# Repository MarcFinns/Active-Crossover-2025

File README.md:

## Active crossover and anti-pop

Used to transform old speakers into active monitors together with a TPA3116 stereo amp board and a 24V power supply from Aliexpress

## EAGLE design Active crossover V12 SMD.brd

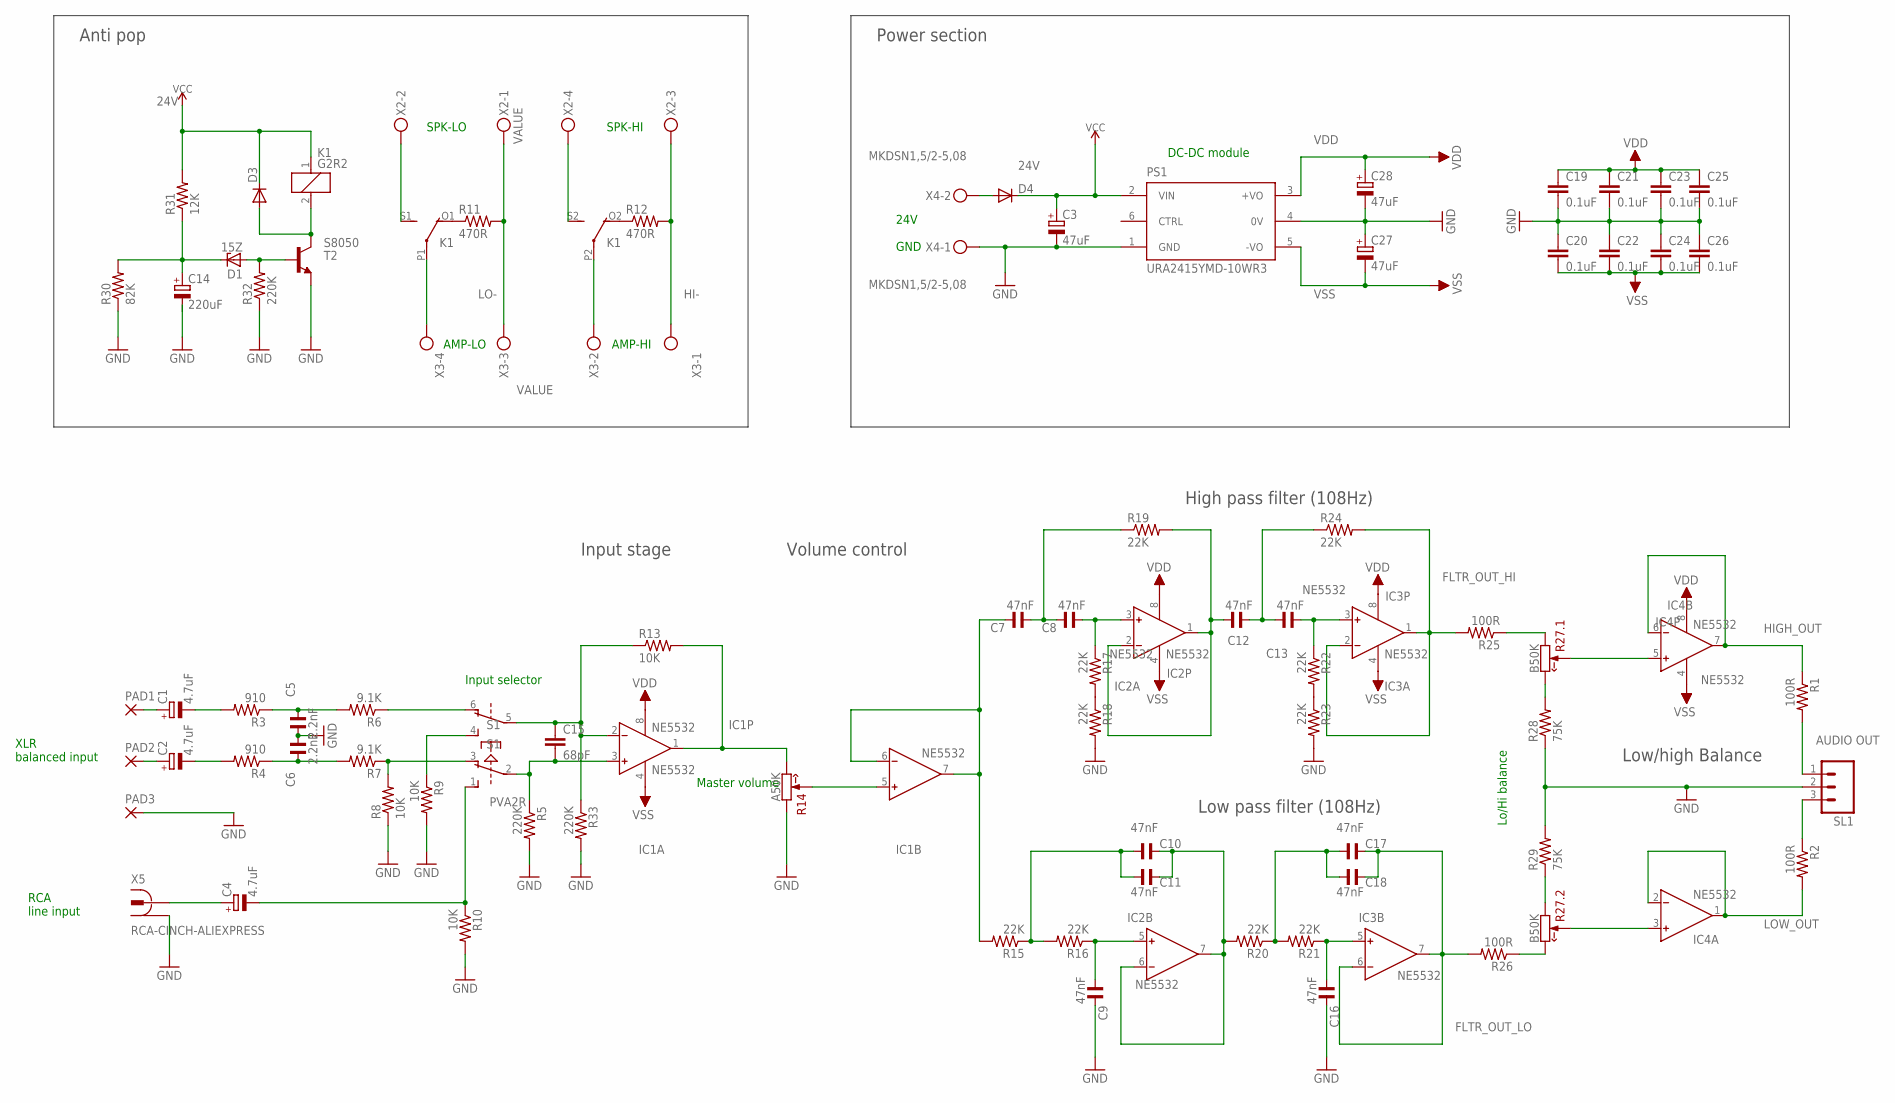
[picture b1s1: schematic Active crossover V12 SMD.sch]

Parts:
C1, C2, C4: 4.7uF; E2-5
C3, C27, C28: 47uF; E2,5-6
C5, C6: 2.2nF; C050-025X072
C7, C8, C9, C10, C11, C12, C13, C16, C17, C18: 47nF; C050-025X072
C14: 220uF; E3,5-8
C15: 68pF; 0603-CAP
C19, C20, C21, C22, C23, C24, C25, C26: 0.1uF; 0603-CAP
D1: 15Z; ZDIO-7.5
D3: DIODESMA-ALT; SMA-DIODE_ALT
D4: DIODESMB; SMB-DIODE
IC1, IC2, IC3, IC4: NE5532; DIL08
K1: G2R2
PAD1, PAD2, PAD3: 3,17/1,3
PS1: URA2415YMD-10WR3; CONV_URA2405YMD-10WR3
R1, R2, R25, R26: 100R; 0204/7
R3, R4: 910; 0204/7
R5, R33: 220K; 0204/7
R6, R7: 9.1K; 0204/7
R8, R9, R10, R13: 10K; 0204/7
R11, R12: 470R; 0204/7
R14: A50K; RV09-SINGLE
R15, R16, R17, R18, R19, R20, R21, R22, R23, R24: 22K; 0204/7
R27: B50K; RK14-DUAL
R28, R29: 75K; 0204/7
R30: 82K; M0805
R31: 12K; M0805
R32: 220K; M0805
S1: PVA2R
SL1: AUDIO OUT; 03P
T2: S8050; SOT23
X2, X3: MKDSN1,5/4-5,08
X4: MKDSN1,5/2-5,08
X5: RCA-CINCH-ALIEXPRESS

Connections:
24V: C3.+, D3.C, D4.C, K1.1, PS1.2 (VIN), R31.2
FLTR_OUT_HI: IC3.1 (OUT), IC3.2 (IN-), R24.2, R25.2
FLTR_OUT_LO: C17.2, C18.2, IC3.6 (IN-), IC3.7 (OUT), R26.2
GND: C3.-, C5.1, C6.2, C9.2, C14.-, C16.2, C19.2, C20.1, C21.2, C22.1, C23.2, C24.1, C25.2, C26.1, C27.+, C28.-, PAD3.1, PS1.1 (GND), PS1.4 (0V), R5.2, R8.1, R9.2, R10.2, R14.1 (CCW), R18.2, R23.2, R28.1, R29.2, R30.1, R32.1, R33.2, SL1.2, T2.2 (E), X4.1, X5.P$1 (1), X5.P$3 (1)
HI-: R12.2, X2.3, X3.1
HIGH_OUT: IC4.6 (IN-), IC4.7 (OUT), R1.1
LO-: R11.2, X2.1, X3.3
LOW_OUT: IC4.1 (OUT), IC4.2 (IN-), R2.2
unnamed: C1.+, PAD1.1
unnamed: C1.-, R3.2
unnamed: R7.1, R8.2, S1.3 (O)
unnamed: C15.1, IC1.2 (IN-), R13.1, R33.1, S1.5
unnamed: C15.2, IC1.3 (IN+), R5.1, S1.2
unnamed: C4.-, R10.1, S1.1 (S)
unnamed: R6.1, S1.6 (O)
unnamed: R9.1, S1.4 (S)
unnamed: IC1.1 (OUT), R13.2, R14.3 (CW)
unnamed: C14.+, D1.C, R30.2, R31.1
unnamed: K1.P1, X3.4
unnamed: D1.A, R32.2, T2.1 (B)
unnamed: D3.A, K1.2, T2.3 (C)
unnamed: IC1.5 (IN+), R14.2 (W)
unnamed: K1.S1 (S), X2.2
unnamed: C16.1, IC3.5 (IN+), R21.1
unnamed: C5.2, R3.1, R6.2
unnamed: C6.1, R4.1, R7.2
unnamed: C10.1, C11.1, R15.1, R16.2
unnamed: C17.1, C18.1, R20.1, R21.2
unnamed: C8.1, IC2.3 (IN+), R17.1
unnamed: C7.1, C8.2, R19.1
unnamed: R27.3 (CCW), R29.1
unnamed: C9.1, IC2.5 (IN+), R16.1
unnamed: R27.1' (CW), R28.2
unnamed: C12.2, IC2.1 (OUT), IC2.2 (IN-), R19.2
unnamed: C12.1, C13.2, R24.1
unnamed: C13.1, IC3.3 (IN+), R22.1
unnamed: C10.2, C11.2, IC2.6 (IN-), IC2.7 (OUT), R20.2
unnamed: K1.O1 (O), R11.1
unnamed: K1.P2, X3.2
unnamed: K1.S2 (S), X2.4
unnamed: K1.O2 (O), R12.1
unnamed: R17.2, R18.1
unnamed: C7.2, IC1.6 (IN-), IC1.7 (OUT), R15.2
unnamed: R22.2, R23.1
unnamed: R25.1, R27.3' (CCW)
unnamed: IC4.5 (IN+), R27.2' (W)
unnamed: IC4.3 (IN+), R27.2 (W)
unnamed: R26.1, R27.1 (CW)
unnamed: C2.+, PAD2.1
unnamed: C2.-, R4.2
unnamed: C4.+, X5.P$2 (2)
unnamed: D4.A, X4.2
unnamed: R1.2, SL1.1
unnamed: R2.1, SL1.3
VDD: C19.1, C21.1, C23.1, C25.1, C28.+, IC1.8 (V+), IC2.8 (V+), IC3.8 (V+), IC4.8 (V+), PS1.3 (+VO)
VSS: C20.2, C22.2, C24.2, C26.2, C27.-, IC1.4 (V-), IC2.4 (V-), IC3.4 (V-), IC4.4 (V-), PS1.5 (-VO)

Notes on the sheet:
XLR balanced input
RCA line input
Input selector
Master volume
AMP-LO
AMP-HI
SPK-LO
SPK-HI
24V GND
DC-DC module
Lo/Hi balance
Anti pop
Power section
Input stage
Volume control
High pass filter (108Hz)
Low pass filter (108Hz)
Low/high Balance

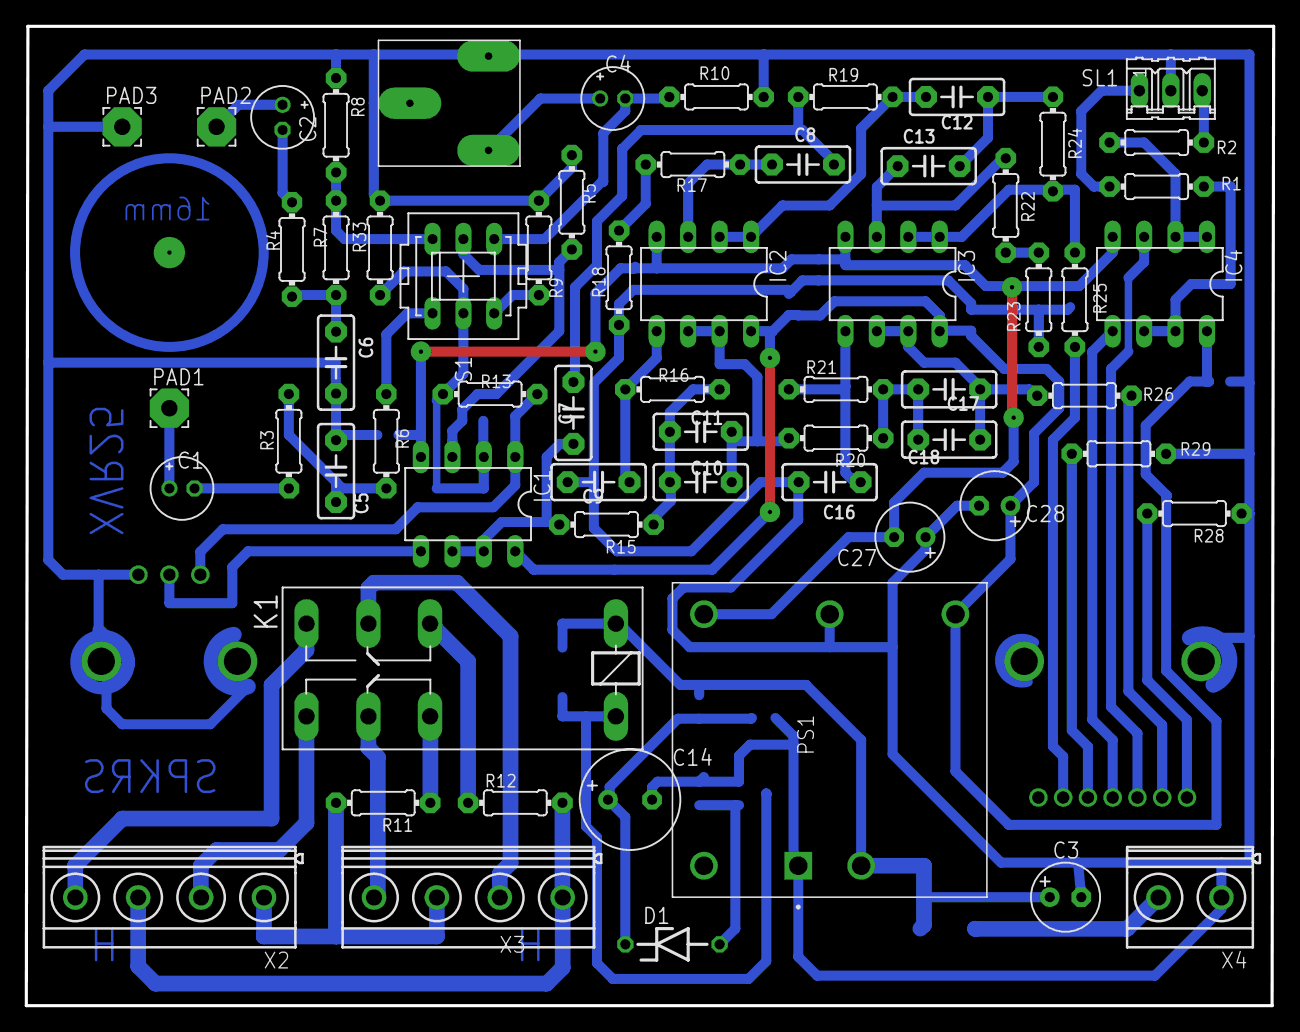
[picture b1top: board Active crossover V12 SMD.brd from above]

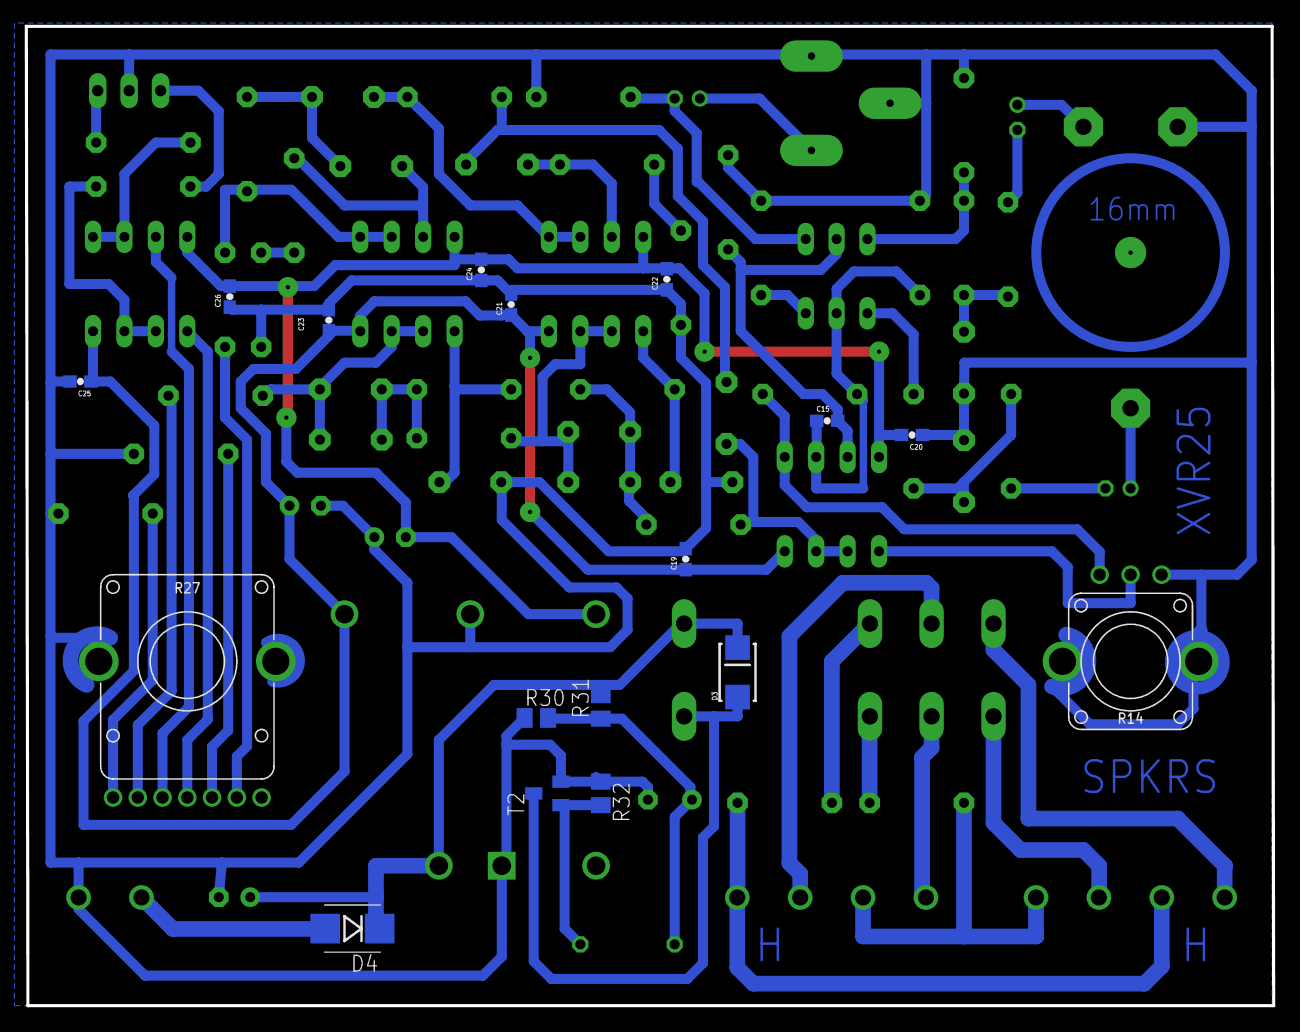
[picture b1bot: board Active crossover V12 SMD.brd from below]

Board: 2 copper layers, 100.8 x 79.1 mm, 80 parts (17 on the bottom side), 56 nets.

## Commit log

2025-01-30 Create list

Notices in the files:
parts and their libraries:
cap-wima: Copyright (C) 2010, Bob Starr
SparkFun-Capacitors: Licensing: CC v3.0 Share-Alike You are welcome to use this library for commercial purposes.
supply4: Copyright (C) 2007, Bob Starr
